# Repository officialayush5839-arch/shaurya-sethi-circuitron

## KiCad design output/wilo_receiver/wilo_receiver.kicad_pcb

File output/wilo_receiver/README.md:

# Wilo Water Pump Automation — Receiver Station HAT (Rev 3.0)

[-success.svg)](#)

Production-ready KiCad hardware project for the **Wilo Water Pump Automation Receiver Station HAT** (Rev 3.0). This board acts as the central automation hub, pairing a **Raspberry Pi Zero 2W**, **SX1278 433 MHz LoRa transceiver**, **ADS1115 16-bit precision ADC**, **dual 10A 250VAC relays**, and **isolated AC voltage and current sensors** into an industrial-grade automation controller.

---

## Visual Showcase

### Full Engineering Schematic Diagram (Rev 3.0 — 7 Functional Blocks)

### High-Resolution 2D Board Layout (Rev 3.0 — 140 mm × 95 mm)

### 3D Raytraced Isometric View

### 3D Raytraced Top-Down View

---

## Key Hardware Architectural Features

1. **100% 5V DC USB-C Main Power**:
   - The entire board's logic, Raspberry Pi Zero 2W, LoRa transceiver, relays, and sensors are powered strictly through the **5V DC USB-C port (`J_USBC`)**.
   - **Zero internal AC-to-DC converter**: keeps the control board low-voltage, cool, and safe to service.
   - Dedicated onboard **AMS1117-3.3V LDO regulator (`U1`)** provides low-noise 3.3V power to the Ra-02 LoRa module and sensitive 3.3V analog rails.

2. **Single Unified Ground Plane Architecture**:
   - The PCB layout features an expanded **140 mm × 95 mm** footprint with a single continuous ground plane for superior signal integrity and low impedance return paths.
   - Eliminates complex slot cutouts and isolation zone boundaries while maintaining generous physical spacing (>6.0 mm clearance) around high-voltage sensor pins and relay traces.

3. **Perimeter & Corner Connector Strategy**:
   - All external terminals, headers, buttons, and jacks are strategically positioned around the board edges and corners for clean enclosure routing and panel mounting:
     - **`J_USBC` (5V Main Power)**: Bottom-left corner (`(12, 82)`).
     - **`J_SMA` (50Ω Antenna)**: Top-left edge (`(10, 30)`).
     - **`J_CT` (3.5mm Current Clamp)**: Mid-left edge (`(11.5, 54)`).
     - **`J1` (RPi Zero 2W 40-Pin Header)**: Top perimeter (`(40, 14)`).
     - **`TB_EXP` (A2/A3 Expansion)**: Top-right edge (`(98, 15)`).
     - **`TB2` (Voltage Sense Only)**: Top-right corner (`(125, 17)`).
     - **`TB3` (Load Out)**: Bottom-right corner (`(125, 76)`).
     - **`SW1` & `SW2`**: Bottom edge manual tactile override controls (`FORCE ON`, `FORCE OFF`).

4. **Sensing & Telemetry Subsystems**:
   - **Mains Voltage Sensing (`TB2`)**: `TB2: SENSE ONLY (NOT POWER)`. Samples 230V AC grid voltage across high-voltage drop resistors (`R_HV1` 41.2kΩ 1W, `R_HV2` 41.2kΩ 1W) through a **ZMPT101B potential transformer (`T1`)** and active LM358 op-amp conditioning into ADS1115 Channel A1.
   - **Motor Current Sensing**: Dual sampling capability using either an external 3.5mm split-core CT clamp (`J_CT`) into ADS1115 Channel A0, or an onboard **ACS712T-30A Hall-effect current sensor (`U3`)**.
   - **Auxiliary Inputs (`TB_EXP`)**: 2-pin screw terminal exposing ADS1115 Channels A2 & A3 for external water pressure, float switches, or temperature probes.

5. **Industrial Load Switching & Protection**:
   - **Dual 10A 250VAC Songle Relays**: `K1` (Wilo Pump) and `K2` (Auxiliary / Motorized Valve).
   - **Galvanic Optical Isolation**: Driven via **PC817 optocouplers (`U5`, `U6`)** with **MMBT3904 NPN transistors (`Q1`, `Q2`)** and flyback protection diodes (`1N4007`).
   - **Transient & Arc Suppression**: Metal Oxide Varistor (**MOV1: 14D471K**) across mains load, plus an RC snubber network (**`R_SNUB` 100Ω 1W + `C_SNUB` 0.1µF 275VAC X2 safety capacitor**).

---

## Hardware Specifications Table

| Parameter | Specification | Notes |
| :--- | :--- | :--- |
| **Board Dimensions** | 140.0 mm × 95.0 mm | 4× M2.5 mounting holes at corners |
| **Layer Count** | 2 Layers | Top: Signal & Silkscreen, Bottom: Unified GND Plane |
| **Copper Weight** | 2.0 oz (70 µm) outer layers | Rated for 10A continuous motor current handling |
| **Substrate & Thickness** | FR4 Standard, 1.6 mm | TG130-140 |
| **Main System Power** | 5V DC @ 2.5A via USB-C (`J_USBC`) | Powers RPi Zero 2W, relays, sensors, logic |
| **Onboard 3.3V Rail** | AMS1117-3.3V (1.0A max) | Low-ESR 10µF input + 22µF output tantalum/ceramic |
| **RF Transceiver** | Ai-Thinker Ra-02 (SX1278 433 MHz LoRa) | 50Ω matched trace to SMA connector (`J_SMA`) |
| **Analog-to-Digital Converter**| TI ADS1115 (16-bit 4-channel I2C ADC) | I2C address `0x48`, pull-ups 4.7kΩ to 3.3V |
| **Voltage Sensor** | ZMPT101B 2mA:2mA Current-Type PT | Isolated AC potential measurement (`TB2`) |
| **Current Sensor** | Allegro ACS712T-30A / CT clamp jack | Hall-effect isolated 66 mV/A + 3.5mm audio jack |
| **Relay Outputs** | 2× Songle SRD-05VDC-SL-C (SPDT 10A) | K1: Pump, K2: Valve/Aux |
| **Status Indicators** | 3× 0805 SMD LEDs | Green: 5V PWR, Blue: 3V3 RF, Amber: PUMP ON |
| **Manual Controls** | 2× 6×6 mm tactile push buttons | SW1: Force ON, SW2: Force OFF |

---

## Quick Start (How to Open in KiCad)

1. Clone or extract this repository to your local computer:
   ```bash
   git clone https://github.com/officialayush5839-arch/Wilo-Receiver-PCB.git
   ```
2. Launch **KiCad 7, 8, 9, or 10**.
3. Select **File → Open Project...** (`Ctrl + O`) and open **`wilo_receiver.kicad_pro`**.
4. In the KiCad Project Manager panel:
   - Double-click **`wilo_receiver.kicad_sch`** to open the modular schematic.
   - Double-click **`wilo_receiver.kicad_pcb`** to open the 140×95 mm PCB layout.
5. In the PCB Editor, press **`Alt + 3`** to view the interactive 3D raytraced model.

---

## Project Structure & Zero-Dependency Portability

```
Wilo-Receiver-PCB/
├── README.md                      # Complete project documentation with embedded graphics
├── wilo_receiver.kicad_pro        # Master KiCad project file
├── wilo_receiver.kicad_pcb        # Production 2-layer PCB layout (140 mm x 95 mm)
├── wilo_receiver.kicad_sch        # Modular schematic diagram (7 framed functional blocks)
├── wilo_receiver.kicad_sym        # Embedded symbol library definitions
├── fp-lib-table                   # Footprint table configured with ${KIPRJMOD}
├── sym-lib-table                  # Symbol table configured with ${KIPRJMOD}
├── bom.csv                        # Full Bill of Materials with references & manufacturer numbers
├── wilo_receiver.net              # Generated KiCad netlist
├── wilo_receiver.pretty/          # Local footprint directory (18 custom .kicad_mod footprints)
├── gerbers/                       # Ready-to-order manufacturing Gerbers and drill files
├── firmware/                      # Companion Raspberry Pi Python firmware & systemd service
├── wilo_receiver_schematic.png    # High-resolution engineering schematic diagram (A3)
├── wilo_receiver_board_top.png    # High-resolution 2D layout graphic
├── wilo_receiver_2d_board.svg     # Scalable Vector Graphic 2D board render
├── wilo_receiver_3d_iso.png       # 3D raytraced isometric render
└── wilo_receiver_3d_top.png       # 3D raytraced top view render
```

---

## Recommended PCB Fabrication Specs (JLCPCB / PCBWay)

- **Layers**: 2 Layers
- **Dimensions**: 140.0 mm × 95.0 mm
- **Material**: FR-4 (TG130–140)
- **Thickness**: 1.6 mm
- **Outer Copper Weight**: 2.0 oz (recommended for 10A relay load paths)
- **Surface Finish**: Lead-Free HASL or ENIG-1U
- **Solder Mask**: Pine Green (or Matte Black)
- **Silkscreen**: Crisp White (zero overlap guaranteed)
- **Min Trace / Space**: 0.25 mm / 0.25 mm (mains traces: 2.0–3.0 mm)

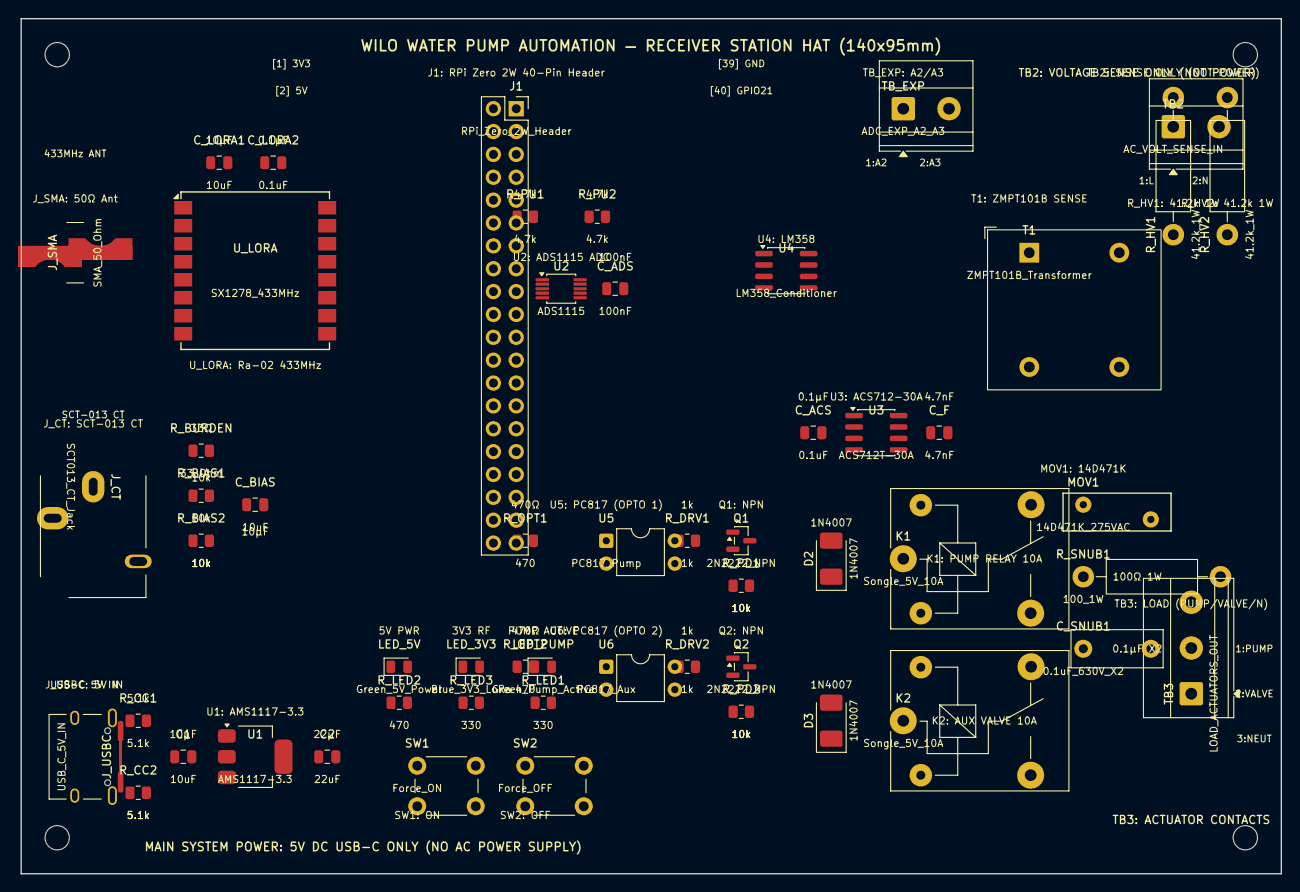
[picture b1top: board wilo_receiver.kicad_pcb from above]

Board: 2 copper layers, 140.0 x 95.0 mm, 55 parts (0 on the bottom side), 47 nets, no tracks yet.

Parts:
C1: 10uF; C_0805_2012Metric
C2: 22uF; C_0805_2012Metric
C_ACS: 0.1uF; C_0805_2012Metric
C_ADS: 100nF; C_0805_2012Metric
C_BIAS: 10uF; C_0805_2012Metric
C_F: 4.7nF; C_0805_2012Metric
C_LORA1: 10uF; C_0805_2012Metric
C_LORA2: 0.1uF; C_0805_2012Metric
C_SNUB1: 0.1uF_630V_X2; C_Rect_L10.0mm_W4.0mm_P7.50mm_MKS4
D2, D3: 1N4007; D_SMA
J1: RPi_Zero_2W_Header; PinSocket_2x20_P2.54mm_Vertical
J_CT: SCT013_CT_Jack; Jack_3.5mm_CUI_SJ1-3513N_Horizontal
J_SMA: SMA_50_Ohm; SMA_Amphenol_132134-10_Vertical
J_USBC: USB_C_5V_IN; USB_C_Receptacle_HRO_TYPE-C-31-M-12
K1, K2: Songle_5V_10A; Relay_SPDT_SANYOU_SRD_Series_Form_C
LED_3V3: Blue_3V3_LoRa; LED_0805_2012Metric
LED_5V: Green_5V_Power; LED_0805_2012Metric
LED_PUMP: Green_Pump_Active; LED_0805_2012Metric
MOV1: 14D471K_275VAC; RV_Disc_D12mm_W4.2mm_P7.5mm
Q1, Q2: 2N2222_NPN; SOT-23
R_BIAS1, R_BIAS2: 10k; R_0805_2012Metric
R_BURDEN: 33_Ohm; R_0805_2012Metric
R_CC1, R_CC2: 5.1k; R_0805_2012Metric
R_DRV1, R_DRV2: 1k; R_0805_2012Metric
R_HV1, R_HV2: 41.2k_1W; R_Axial_DIN0411_L9.9mm_D3.6mm_P15.24mm_Horizontal
R_LED1, R_LED3: 330; R_0805_2012Metric
R_LED2: 470; R_0805_2012Metric
R_OPT1, R_OPT2: 470; R_0805_2012Metric
R_PD1, R_PD2: 10k; R_0805_2012Metric
R_PU1, R_PU2: 4.7k; R_0805_2012Metric
R_SNUB1: 100_1W; R_Axial_DIN0411_L9.9mm_D3.6mm_P15.24mm_Horizontal
SW1: Force_ON; SW_PUSH_6mm
SW2: Force_OFF; SW_PUSH_6mm
T1: ZMPT101B_Transformer; Transformer_Zeming_ZMPT101K
TB2: AC_VOLT_SENSE_IN; TerminalBlock_Phoenix_MKDS-1,5-2-5.08_1x02_P5.08mm_Horizont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
TB3: LOAD_ACTUATORS_OUT; TerminalBlock_Phoenix_MKDS-1,5-3-5.08_1x03_P5.08mm_Horizont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
TB_EXP: ADC_EXP_A2_A3; TerminalBlock_Phoenix_MKDS-1,5-2-5.08_1x02_P5.08mm_Horizont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
U1: AMS1117-3.3; SOT-223-3_TabPin2
U2: ADS1115; MSOP-10_3x3mm_P0.5mm
U3: ACS712T-30A; SOIC-8_3.9x4.9mm_P1.27mm
U4: LM358_Conditioner; SOIC-8_3.9x4.9mm_P1.27mm
U5: PC817_Pump; DIP-4_W7.62mm
U6: PC817_Aux; DIP-4_W7.62mm
U_LORA: SX1278_433MHz; Ai-Thinker-Ra-01-LoRa

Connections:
+3V3_LORA: C2.1, C_LORA1.1, C_LORA2.1, R_LED3.1, U1.2, U_LORA.9
+3V3_RPI: J1.1, J1.17, R_PU1.2, R_PU2.2
+5V: C1.1, C_ACS.1, C_ADS.1, D2.1, D3.1, J1.2, J1.4, J_USBC.A4, J_USBC.A9, J_USBC.B4, J_USBC.B9, K1.1, K2.1, R_BIAS1.1, R_LED2.1, U1.3, U2.8, U3.8, U4.8, U5.4, U6.4
AC_L_IN: K2.3, R_HV1.1, TB2.1, U3.1, U3.2
AC_L_PUMP: K1.3, MOV1.1, R_SNUB1.1, U3.3, U3.4
AC_N_IN: T1.2, TB2.2, TB3.3
AC_PUMP_OUT: C_SNUB1.2, K1.4, MOV1.2, TB3.1
AC_VALVE_OUT: K2.4, TB3.2
ADC_A0: J_CT.T, R_BURDEN.2, U2.4, U3.7
ADC_A1: U2.5, U4.1
ADC_A2: TB_EXP.1, U2.6
ADC_A3: TB_EXP.2, U2.7
BTN_FORCE_OFF: J1.29, SW2.1
BTN_FORCE_ON: J1.15, SW1.1
CT_BIAS: C_BIAS.1, J_CT.S, R_BIAS1.2, R_BIAS2.1, R_BURDEN.1
GND: C1.2, C2.2, C_ACS.2, C_ADS.2, C_BIAS.2, C_F.2, C_LORA1.2, C_LORA2.2, J1.6, J1.9, J1.14, J1.20, J1.25, J1.30, J1.34, J1.39, J_SMA.2, J_USBC.A1, J_USBC.A12, J_USBC.B1, J_USBC.B12, J_USBC.SH, LED_3V3.2, LED_5V.2, LED_PUMP.2, Q1.2, Q2.2, R_BIAS2.2, R_CC1.2, R_CC2.2, R_PD1.2, R_PD2.2, SW1.2, SW2.2, T1.4, U1.1, U2.1, U2.3, U3.5, U4.3, U4.4, U4.5, U5.2, U6.2, U_LORA.1, U_LORA.8, U_LORA.16
I2C_SCL: J1.5, R_PU2.1, U2.10
I2C_SDA: J1.3, R_PU1.1, U2.9
LED_3V3_MID: LED_3V3.1, R_LED3.2
LED_5V_MID: LED_5V.1, R_LED2.2
LED_DRIVE: LED_PUMP.1, R_LED1.2
LED_PUMP_RUN: J1.31, R_LED1.1
LORA_DIO0: J1.18, U_LORA.7
LORA_RST: J1.22, U_LORA.6
unnamed: J_USBC.A5, R_CC1.1
unnamed: J_USBC.B5, R_CC2.1
unnamed: C_F.1, U3.6
unnamed: R_HV1.2, R_HV2.1
unnamed: R_HV2.2, T1.1
unnamed: U4.6, U4.7
unnamed: T1.3, U4.2
unnamed: R_DRV1.1, U5.3
unnamed: D2.2, K1.2, Q1.3
unnamed: R_DRV2.1, U6.3
unnamed: D3.2, K2.2, Q2.3
OPT1_IN: R_OPT1.2, U5.1
OPT2_IN: R_OPT2.2, U6.1
Q1_BASE: Q1.1, R_DRV1.2, R_PD1.1
Q2_BASE: Q2.1, R_DRV2.2, R_PD2.1
RELAY1_CTRL: J1.11, R_OPT1.1
RELAY2_CTRL: J1.13, R_OPT2.1
RF_ANT: J_SMA.1, U_LORA.15
SNUB1_MID: C_SNUB1.1, R_SNUB1.2
SPI0_CE0: J1.24, U_LORA.13
SPI0_MISO: J1.21, U_LORA.11
SPI0_MOSI: J1.19, U_LORA.12
SPI0_SCLK: J1.23, U_LORA.10

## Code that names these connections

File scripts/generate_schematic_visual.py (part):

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
    left_pins = [
        ("1", "+3V3_RPI", "3.3V Power"),
        ("3", "I2C_SDA", "GPIO 2 (SDA)"),
        ("5", "I2C_SCL", "GPIO 3 (SCL)"),
        ("7", "NC", "GPIO 4"),
        ("9", "GND", "Ground"),
        ("11", "RELAY1_CTRL", "GPIO 17"),
        ("13", "RELAY2_CTRL", "GPIO 27"),
        ("15", "LED_PUMP_RUN", "GPIO 22"),
        ("17", "+3V3_RPI", "3.3V Power"),
        ("19", "SPI0_MOSI", "GPIO 10"),
        ("21", "SPI0_MISO", "GPIO 9"),
        ("23", "SPI0_SCLK", "GPIO 11"),
        ("25", "GND", "Ground"),
        ("27", "NC", "ID_SD"),
        ("29", "BTN_FORCE_ON", "GPIO 5"),
        ("31", "BTN_FORCE_OFF", "GPIO 6"),
        ("33", "NC", "GPIO 13"),
        ("35", "NC", "GPIO 19"),
        ("37", "NC", "GPIO 26"),
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        ("12", "NC", "GPIO 18"),
        ("14", "GND", "Ground"),
        ("16", "NC", "GPIO 23"),
        ("18", "LORA_RST", "GPIO 24"),
        ("20", "GND", "Ground"),
        ("22", "LORA_DIO0", "GPIO 25"),
        ("24", "SPI0_CE0", "GPIO 8"),
        ("26", "NC", "GPIO 7"),
        ("28", "NC", "ID_SC"),
        ("30", "GND", "Ground"),
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    draw_led(led_x + 90, 290, "LED_3V3", "Blue", points_down=True)
    draw_gnd(led_x + 90, 325)

    draw_net_label(sw_x - 34, 460, "LED_PUMP_RUN", align="rm")
    draw.line([sw_x - 30, 460, sw_x + 10, 460], fill=WIRE_CLR, width=2)
    draw_resistor(sw_x + 40, 460, "R_LED1", "330Ω", horiz=True)
    draw.line([sw_x + 70, 460, sw_x + 110, 460], fill=WIRE_CLR, width=2)
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    draw.text((tb2_x + 55, tb2_y + 44), "5.08mm 2-Pin", fill="#555555", font=font_small, anchor="mm")
    draw.text((tb2_x + 25, tb2_y + 80), "1 (L)", fill="#B22222", font=font_pin, anchor="mm")
    draw.text((tb2_x + 25, tb2_y + 120), "2 (N)", fill="#000088", font=font_pin, anchor="mm")
    draw_net_label(tb2_x - 10, tb2_y + 80, "AC_L_IN", align="rm", bg="#FADBD8")
    draw_net_label(tb2_x - 10, tb2_y + 120, "AC_N_IN", align="rm", bg="#EBF5FB")

    # High Voltage Resistors
    draw.line([tb2_x + 110, tb2_y + 80, tb2_x + 160, tb2_y + 80], fill=WIRE_CLR, width=2)
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
    # Output to ADC_A1
    draw.line([u4_x + 75, u4_y, u4_x + 140, u4_y], fill=WIRE_CLR, width=2)
    draw_net_label(u4_x + 144, u4_y, "ADC_A1", align="lm")

    # -------------------------------------------------------------
    # 6. BLOCK 4: 5V DC USB-C POWER & AMS1117-3.3V LDO
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    draw.text((exp_x + 85, exp_y + 44), "5.08mm 2-Pin Screw", fill="#555555", font=font_small, anchor="mm")
    draw.text((exp_x + 35, exp_y + 80), "Pin 1", fill=PIN_CLR, font=font_pin, anchor="lm")
    draw.text((exp_x + 35, exp_y + 115), "Pin 2", fill=PIN_CLR, font=font_pin, anchor="lm")
    draw_net_label(exp_x - 15, exp_y + 80, "ADC_A2", align="rm")
    draw_net_label(exp_x - 15, exp_y + 115, "ADC_A3", align="rm")
    draw.line([exp_x - 15, exp_y + 80, exp_x, exp_y + 80], fill=WIRE_CLR, width=2)
    draw.line([exp_x - 15, exp_y + 115, exp_x, exp_y + 115], fill=WIRE_CLR, width=2)

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
    draw.text((acs_x + 15, acs_y + 140), "IP+ [1,2]", fill=PIN_CLR, font=font_pin, anchor="lm")
    draw.text((acs_x + 15, acs_y + 240), "IP- [3,4]", fill=PIN_CLR, font=font_pin, anchor="lm")
    draw_net_label(acs_x - 10, acs_y + 140, "AC_L_IN", align="rm", bg="#FADBD8")
    draw_net_label(acs_x - 10, acs_y + 240, "AC_L_PUMP", align="rm", bg="#FADBD8")
    draw.line([acs_x - 10, acs_y + 140, acs_x, acs_y + 140], fill=WIRE_CLR, width=3)
    draw.line([acs_x - 10, acs_y + 240, acs_x, acs_y + 240], fill=WIRE_CLR, width=3)

    acs_sec = [
        ("VCC [Pin 8]", 120, "+5V"),
        ("VOUT [Pin 7]", 190, "ADC_A0"),
        ("FILTER [Pin 6]", 260, "FILTER"),
        ("GND [Pin 5]", 330, "GND"),
    ]
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        elif net == "GND":
            draw_gnd(acs_x + acs_w + 30, py)
        elif net == "ADC_A0":
            draw_net_label(acs_x + acs_w + 34, py, "ADC_A0", align="lm")
        elif net == "FILTER":
            draw_capacitor(acs_x + acs_w + 80, py, "C_F", "4.7nF", horiz=False)
            draw_gnd(acs_x + acs_w + 80, py + 30)
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        # Contact Pins: COM, NO
        draw.text((relay_x + 220, relay_y + 75), "COM", fill=PIN_CLR, font=font_pin, anchor="rm")
        draw.text((relay_x + 220, relay_y + 125), "NO", fill=PIN_CLR, font=font_pin, anchor="rm")
        draw_net_label(relay_x + 240, relay_y + 75, "AC_L_PUMP", align="lm", bg="#FADBD8")
        draw_net_label(relay_x + 240, relay_y + 125, load_net, align="lm", bg="#FADBD8")

    # Draw Relay 1 (Wilo Pump)
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    draw.text((prot_x + 240, prot_y + 25), "TRANSIENT & SNUBBER NETWORK", fill="#000088", font=font_sec_hdr, anchor="mm")

    # MOV1 Varistor (14D471K)
    draw_net_label(prot_x + 80, prot_y + 80, "AC_L_PUMP", align="rm", bg="#FADBD8")
    draw_resistor(prot_x + 130, prot_y + 140, "MOV1", "14D471K (470V)", horiz=False)
    draw_net_label(prot_x + 80, prot_y + 200, "AC_N_IN", align="rm", bg="#EBF5FB")
    draw.line([prot_x + 80, prot_y + 80, prot_x + 130, prot_y + 110], fill=WIRE_CLR, width=2)
    draw.line([prot_x + 80, prot_y + 200, prot_x + 130, prot_y + 170], fill=WIRE_CLR, width=2)

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    draw.text((tb3_x + 120, tb3_y + 55), "10A 250VAC Screw Terminal", fill="#555555", font=font_small, anchor="mm")

    tb3_pins = [
        ("Pin 1: PUMP", 110, "AC_PUMP_OUT"),
        ("Pin 2: VALVE", 170, "AC_VALVE_OUT"),
        ("Pin 3: NEUT", 230, "AC_N_IN"),
    ]
    for pname, py_rel, net in tb3_pins:
        py = tb3_y + py_rel
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

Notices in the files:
output/wilo_receiver/README.md:
License: MIT
